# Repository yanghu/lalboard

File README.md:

##### lalboard - A 3D-printed keyboard inspired by the DataHand.

Note: The v2 branch has been deprecated in favor of the [v2_no_stls](https://github.com/JesusFreke/lalboard/tree/v2_no_stls) branch.

The new branch has the exported stls in a separate repository, to help avoid large checkouts when cloning
the base repository.

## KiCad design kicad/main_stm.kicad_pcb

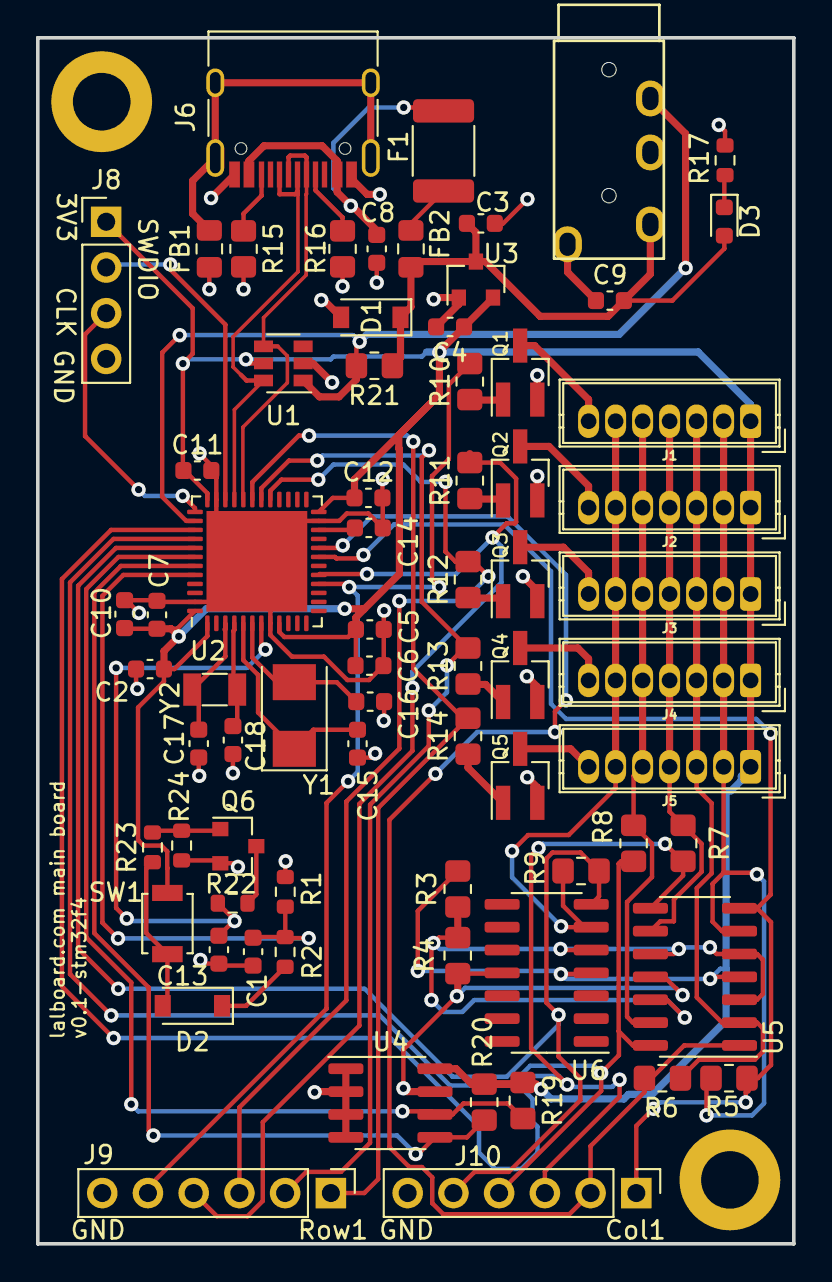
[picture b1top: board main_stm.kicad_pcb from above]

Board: 2 copper layers, 42.0 x 67.0 mm, 74 parts (0 on the bottom side), 53 nets.

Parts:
C1, C7: 10uF; C_0603_1608Metric
C2, C6, C8, C9, C10, C11, C12, C13: 0.1uF; C_0603_1608Metric
C3, C4, C5: 1uF; C_0603_1608Metric
C14: 4.7uF; C_0603_1608Metric
C15, C16: 20pF; C_0603_1608Metric
C17, C18: 1.5pF; C_0603_1608Metric
D1: SMF9.0CA; D_SOD-123
D2: 1N4148; D_SOD-123
D3: LED; LED_0603_1608Metric
F1: JK-MSMD050; Fuse_1812_4532Metric_Pad1.30x3.40mm_HandSolder
FB1, FB2: ACML-0805-500-T; L_0805_2012Metric_Pad1.15x1.40mm_HandSolder
H1, H2: MountingHole_Pad; MountingHole_3.2mm_M3_DIN965_Pad
J1, J2, J3, J4, J5: Conn_01x07; JST_ZH_B7B-ZR_1x07_P1.50mm_Vertical
J6: TYPE-C-31-M-12; USB_C_Receptacle_HRO_TYPE-C-31-M-12
J7: AudioJack4; TRRS-PJ-320Atrrs
J8: Conn_01x04; PinHeader_1x04_P2.54mm_Vertical
J9, J10: Conn_01x06; PinHeader_1x06_P2.54mm_Vertical
Q1, Q2, Q3, Q4, Q5: Q_NPN_BEC; SOT-23_Handsoldering
Q6: MMBT3904; SOT-23
R1: 1M; R_0603_1608Metric
R2: 330k; R_0603_1608Metric
R3: 100k; R_0805_2012Metric_Pad1.20x1.40mm_HandSolder
R4: 390k; R_0805_2012Metric_Pad1.20x1.40mm_HandSolder
R5, R6, R7, R8, R9: 2k; R_0805_2012Metric_Pad1.20x1.40mm_HandSolder
R10, R11, R12, R13, R14: 1.5k; R_0805_2012Metric_Pad1.20x1.40mm_HandSolder
R15, R16: 5.1k; R_0805_2012Metric_Pad1.20x1.40mm_HandSolder
R17: 470; R_0603_1608Metric
R19, R20: 4.7k; R_0805_2012Metric_Pad1.20x1.40mm_HandSolder
R21: 10k; R_0805_2012Metric_Pad1.20x1.40mm_HandSolder
R22: 100; R_0603_1608Metric
R23: 2.2k; R_0603_1608Metric
R24: 47k; R_0603_1608Metric
SW1: SW_Push; SW_SPST_B3U-1000P
U1: SRV05-4; SOT-23-6
U2: STM32F411CCUx; QFN-48-1EP_7x7mm_P0.5mm_EP5.6x5.6mm
U3: XC6206PxxxMR; SOT-23
U4: CAT24C256; SOIC-8_3.9x4.9mm_P1.27mm
U5, U6: LMV324; SOIC-14_3.9x8.7mm_P1.27mm
Y1: 8MHz; Crystal_SMD_5032-2Pin_5.0x3.2mm
Y2: 32.768KHz; Crystal_SMD_3215-2Pin_3.2x1.5mm

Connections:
+3V3: C2.1, C4.1, C5.1, C6.1, C7.1, C10.1, C11.1, C12.1, J1.1, J2.1, J3.1, J4.1, J5.1, J8.1, R3.1, R19.1, R20.1, SW1.1, U1.5, U2.1, U2.9, U2.24, U2.36, U2.48, U3.2, U4.8, U5.4, U6.4
+5V: C3.1, C9.2, D1.1, D3.2, FB2.1, J7.T, R21.1, U3.3
/AMP_REF: R3.2, R4.1, U5.3, U5.5, U5.10, U5.12, U6.5
/COL1: J1.2, J2.2, J3.2, J4.2, J5.2, R5.2, U5.6
/COL1_AMP: J10.1, R5.1, U2.19, U5.7
/COL2: J1.3, J2.3, J3.3, J4.3, J5.3, R6.2, U5.2
/COL2_AMP: J10.2, R6.1, U2.20, U5.1
/COL3: J1.4, J2.4, J3.4, J4.4, J5.4, R7.2, U5.9
/COL3_AMP: J10.3, R7.1, U2.39, U5.8
/COL4: J1.5, J2.5, J3.5, J4.5, J5.5, R8.2, U5.13
/COL4_AMP: J10.4, R8.1, U2.40, U5.14
/COL5: J1.6, J2.6, J3.6, J4.6, J5.6, R9.2, U6.6
/COL5_AMP: J10.5, R9.1, U2.41, U6.7
/D+: J6.A6, J6.B6, U1.6, U2.33
/D-: J6.A7, J6.B7, U1.4, U2.32
/ROW1: J9.1, R14.2, U2.31
/ROW2: J9.2, R13.2, U2.30
/ROW3: J9.3, R12.2, U2.29
/ROW4: J9.4, R11.2, U2.17
/ROW5: J9.5, R10.2, U2.16
/SCL: R19.2, U2.42, U4.6
/SDA: R20.2, U2.43, U4.5
/SWCLK: J8.3, U2.37
/SWDIO: J8.2, U2.34
/U1TX: J7.R2, R21.2, U1.1, U2.38
/stm32f411/BOOT0: C1.1, R1.1, R2.1, U2.44
/stm32f411/NRST: C13.2, R22.1, U2.7
/stm32f411/VCAP1: C14.2, U2.22
GND: C1.2, C2.2, C3.2, C4.2, C5.2, C6.2, C7.2, C8.2, C9.1, C10.2, C11.2, C12.2, C13.1, C14.1, C15.2, C16.2, C17.2, C18.2, D1.2, FB1.2, H1.1, H2.1, J6.A1, J6.A12, J6.B1, J6.B12, J7.S, J8.4, J9.6, J10.6, Q1.2, Q2.2, Q3.2, Q4.2, Q5.2, Q6.2, R1.2, R4.2, R15.2, R16.2, R17.1, R24.2, U1.2, U2.8, U2.23, U2.35, U2.47, U2.49, U3.1, U4.1, U4.2, U4.3, U4.4, U4.7, U5.11, U6.11
unnamed: C8.1, F1.2, J6.A4, J6.A9, J6.B4, J6.B9
unnamed: C15.1, U2.5, Y1.1
unnamed: C16.1, U2.6, Y1.2
unnamed: C17.1, U2.3, Y2.1
unnamed: C18.1, U2.4, Y2.2
unnamed: D2.1, R2.2
unnamed: D2.2, R23.1, SW1.2
unnamed: D3.1, R17.2
unnamed: F1.1, FB2.2
unnamed: FB1.1, J6.S1
unnamed: J1.7, Q1.3
unnamed: J2.7, Q2.3
unnamed: J3.7, Q3.3
unnamed: J4.7, Q4.3
unnamed: J5.7, Q5.3
unnamed: J6.A5, R16.1
unnamed: J6.B5, R15.1
unnamed: Q1.1, R10.1
unnamed: Q2.1, R11.1
unnamed: Q3.1, R12.1
unnamed: Q4.1, R13.1
unnamed: Q5.1, R14.1
unnamed: Q6.1, R23.2, R24.1
unnamed: Q6.3, R22.2

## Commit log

2021-03-12 Add a new "export_parts.py" script, and regenerate all the .stls
2021-03-12 Add an extra .1mm of height to the top of the cluster
    This ensures there are 2 .2mm layers on top of the PTs/LEDs.
2021-03-12 Flatten out the bottom of the key well and shorten it by .6mm
    This truncates the "V" bottom, so we can shorten the bottom of the key well
    a bit.
    This will make the outside bottoms of the keywell nearly flush with the
    back of the pcb, to enable the use of a 90 degree connector, that would
    otherwise intersect the keywell sticking out past the pcb.
    This also has some other minor tweaks to ensure horizontal surfaces are
2021-03-12 Spread out the optical components for the north key
    This gives enough room to place a 90 degree connector on the back
2021-03-12 Make the screw bases a bit thinner
    This gives more room for adjacent bases at the back of the clusters
2021-03-12 Bring in the width of the screw base support even more
    This allows yet closer spacing of 2 adjacent support bases (and thus,
    clusters).
2021-03-13 Ensure the cluster part has the cutout for the connector legs
2021-03-15 Fix the orientation of the magnet void in the base for the screw supports
    The void was flipped vertically, so that the widening insertion taper was
    at the bottom of the hole. This also embiggens the holes slightly, to make
    sure they're able to slip in.
2021-03-15 Add the ability to export sketches as .dxf to export_parts.py
    This also updates all the exported parts files.
2021-03-15 Fix the pad sizes on the cluster pcb design
    The custom sizes had apparently gotten lost in the last commit
    for the kicad stuff.
2021-03-15 Remove the front nubbins of the cluster pcb
    They were originally intended to be held down by a clip in the front, but
    that's not really needed now, with the screw holding the pcb down.
2021-03-15 Ensure all 4 bottom vertical edges of the north keywell are filleted
    This ensures it can fit into the routed hole in the PCB, since it will have
    radiused corners from the milling operation
2021-03-15 Fillet the post and corresponding hole in the cluster for the center key
    This ensures the center key post will fit through the milled hole with
    radiused corners in the PCB.
2021-03-15 Don't fillet the center key hole in the cluster
    Only the center key post itself needs to be Filleted. The hole itself can
    remain square. The corners provide a good place for the slicer to place a
    seam, where it won't interfere with the fit of the key.
2021-03-15 Fillet the center hole in the cluster pcb, and adjust its offset
2021-03-15 Fillet the internal corners of the square protrusion on the back of the pcb
    This ensures all of the internal corners are filleted, for consistency.
2021-03-16 Move the cluster pcb connector back as far as possible
    Now that we've switched to the horizontal connector, we can push the
    connector back a bit, since it requires less clearance behind it.
    I *think* this gets the connector far away enough (barely) from the LED
    and PT for the central key that the wire can be plugged in.
2021-03-16 Update the kicad design for the finger cluster
    This brings the PCB design up to par with the current cluster design.
2021-03-17 Update kicad design for finger cluster
    This adds ground/+5v planes, some thicker traces, and moves the +5v pin
    to pin 1 of the connector.
    Thanks to @rutgervana for taking a look at the design and making
    suggestions/showing example improvements.
2021-03-17 Rotate the cluster pcb part by 180, and tweak how the sketch is created
    This matches the orientation used in the kicad design.
    Kicad didn't like the previous dxf export for some reason. But with the
    sketch defined this way, it seems to work fine.
2021-03-17 Rename cluster_assembly to cluster_body_assembly
    This clears the way for a new cluster_assembly that has all of the keys,
    supports, etc.
2021-03-17 Rename cluster_key_long to cluster_key_tall
    "tall" is the more appropriate opposite of "short" in this context.
2021-03-17 Use cardinal directions as names for the cluster side key bases
    I think this is a bit clearer, and is the nomenclature I usually use when
    referring to a specific key.
2021-03-17 Extract the screw nut design out to a separate method in lalboard.py
    This allows it to be used in other assemblies without having to specify
    its parameters in multiple places.
2021-03-17 Add a screw_support assembly
2021-03-18 Create a cluster assembly, with all the cluster-related parts in-situ
2021-03-18 Add support for generating various exports for assemblies in export_parts.py
    This will export an assembly as an stl, an f3d, and to a specific
    fusion 360 cloud instance (which can then be shared via link, for viewing
    on the web by anyone)
2021-03-18 Add a couple of links to the readme
2021-03-18 Remove the redundant run_design parameters from the various part files
    I thought I had already removed all those. Not sure what happened there.
2021-03-18 Rename "full_thumb" design method to "thumb_assembly"
    This makes it more consistent with the finger cluster naming
2021-03-18 Fix the key alignment in the thumb cluster assemblies, and re-enable them
2021-03-19 Remove the thumb clip
    Instead, we'll add screws to secure the pcb
2021-03-19 Add nut recesses in the thumb clusters, for screws to hold down the PCB
2021-03-19 Switched to using few childrenless copies in the thumb cluster
    This helps bring the runtime down to a more reasonable level, when running
    the thumb cluster with the full component tree.
    (e.g. .create_occurrence(create_children=True))
2021-03-19 Add the screw holes to the thumb pcbs
2021-03-19 Add a way to specify which parts to export in export_parts.stl
2021-03-19 Add a virtual "locating pin" to the cluster pcb sketch
    This gives a reference point for the origin of the sketch, so the import
    location can be set correctly when importing the outline into kicad.
    Basically, you set the grid origin in kicad to the center of the circle
    (assuming the locating pin is already in kicad) and then make a note of
    the coordinates of that point. And then, when importing the outline, you
    can specify those coordinates as the location, to ensure the origin of the
2021-03-19 Fix how assemblies are exported to the fusion cloud
2021-03-19 Add _sketch parts for the thumb pcbs, to generate the outline .dxf files.
2021-03-20 Add a bit more space at the lower outer part of the pcb
    This gives more space to get a trace out of that little cramped area
    in the bottom
2021-03-20 Fillet the remaining sharp corners on the thumb cluster
    It seems silly to have 2 sharp corners, with the rest being filleted
2021-03-20 Add support for the filleted key wells to vertical_key_base
    Also refactor base_cluster_design to use this
2021-03-20 Fillet the keywells on the thumb clusters
2021-03-20 Do some shallow copies in thumb_pcb
    This significantly improves run time when creating the pcb with
    "create_children=True"
2021-03-20 Add a fillet to the attachment cutouts on the thumb pcb
2021-03-20 Add a fillet to the cutout in the thumb pcb for the down key
    This also fillets the sticky-down part of the keywell for the down-key,
    to match the fillet in the pcb.
2021-03-22 Tweak the screw positions for the thumb cluster
    Minor tweaks to improve the pcb placement of the screw holes
2021-03-22 Fix thumb_pcb_right_sketch.py
    It was mirrored, like the left clustered.
2021-03-22 Minor tweaks to the cluster pcb
    - Move the identifying text to the bottom layer
    - Disable some unused layers
    - Move the design so that the import position is at an even (150, 100)
2021-03-22 Update the design of the left thumb cluster pcb
2021-03-22 Update the design of the right thumb cluster pcb
2021-03-22 Update all the exported stls, etc.
2021-03-22 Fix the thumb assemblies
    There was something funky going on with the Group component
2021-03-22 Fix up the cluster and thumb_cluster_left pcbs
    Some of the nets for the pours and screw holes had gotten unassigned
    somehow
2021-03-22 Add screw supports to the thumb assemblies
2021-03-22 Update the exported thumb parts
2021-03-22 Minor updates to the readme
    Added links to the cluster assemblies, and added some section headers.
2021-03-22 Extend the screw hole in the thumb clusters
    This adds some space for the screw behind the nut.
2021-04-28 Deprecate the v2 branch
2021-05-13 Add stm32 version of main board
2021-05-13 add automation config
2021-05-13 update kicad/.gitignore to exclude some kicad files
2021-05-13 adjust silkscreen of main stm pcb
2021-05-16 minor fix to stm32 schema
2021-05-17 use absolute path for stls repo
2021-05-17 shrink size of key post and center key pole a little bit
2021-06-05 adjust stl size
2021-06-12 adjust dimensions of magnet cutout and post size
2021-06-12 make horizontal rotated cutout inside larger
2021-06-14 fix export parts
2021-06-16 scale handrest model and move magnet cutout by 1mm
